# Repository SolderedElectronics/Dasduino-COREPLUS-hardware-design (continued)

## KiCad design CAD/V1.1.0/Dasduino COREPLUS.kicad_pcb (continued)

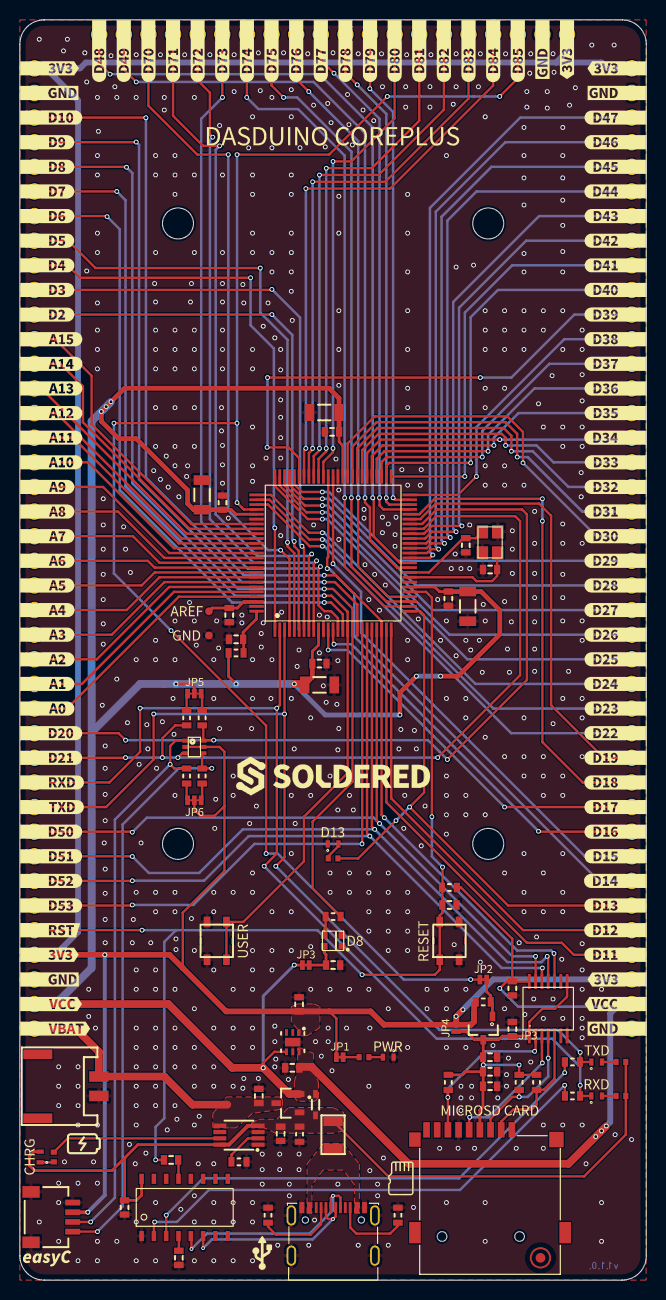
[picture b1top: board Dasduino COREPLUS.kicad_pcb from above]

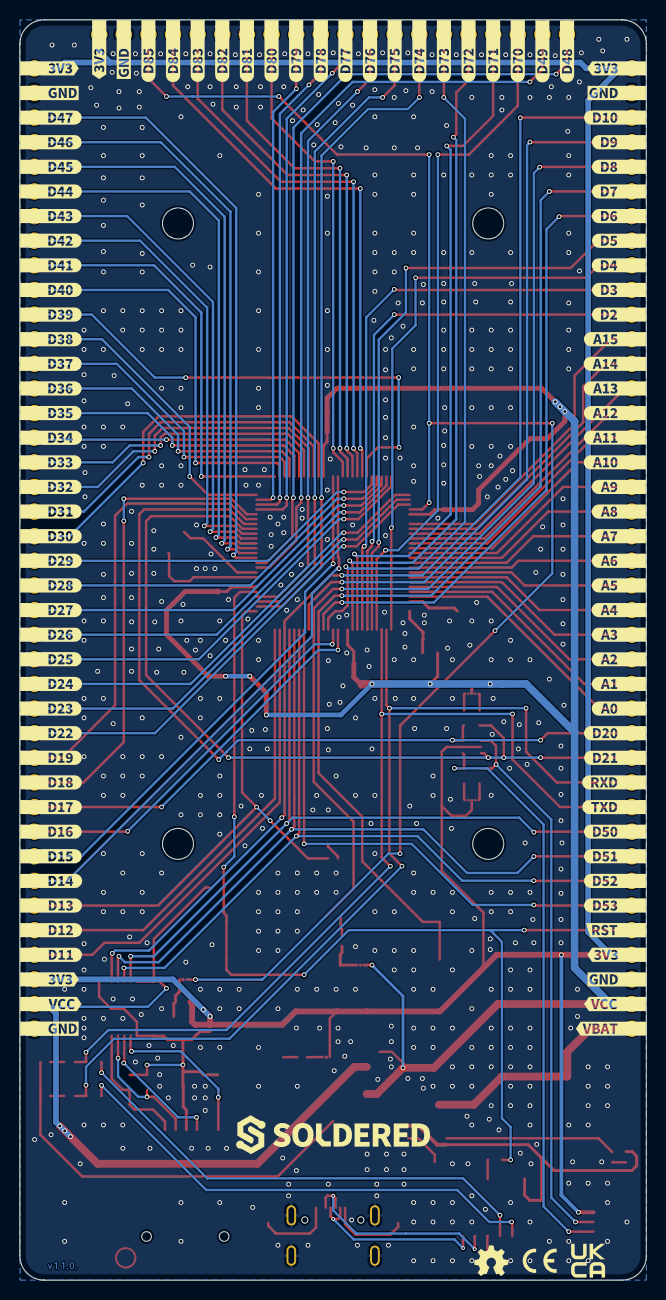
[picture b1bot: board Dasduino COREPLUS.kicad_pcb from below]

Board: 2 copper layers, 64.6 x 130.0 mm, 307 parts (104 on the bottom side), 127 nets.

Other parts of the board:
Ref**: Val**; Version1.1.0
kibuzzard-63D0D5A9: G***; kibuzzard-63D0D5A9
kibuzzard-63D0D5D8: G***; kibuzzard-63D0D5D8
kibuzzard-63D0D6BF: G***; kibuzzard-63D0D6BF
kibuzzard-63D0D6CA: G***; kibuzzard-63D0D6CA
kibuzzard-63D0D7E7: G***; kibuzzard-63D0D7E7
kibuzzard-63D0D78E: G***; kibuzzard-63D0D78E
kibuzzard-63D0D81B: G***; kibuzzard-63D0D81B
kibuzzard-63D0D88E: G***; kibuzzard-63D0D88E
kibuzzard-63D0DB6C: G***; kibuzzard-63D0DB6C
kibuzzard-63D0DB7A: G***; kibuzzard-63D0DB7A
kibuzzard-63D0DB98: G***; kibuzzard-63D0DB98
kibuzzard-63D0DBA8: G***; kibuzzard-63D0DBA8
kibuzzard-63D0DBC0: G***; kibuzzard-63D0DBC0
kibuzzard-63D0DBF0, kibuzzard-63D0DBF0#2: G***; kibuzzard-63D0DBF0
kibuzzard-63DB5B79: G***; kibuzzard-63DB5B79
kibuzzard-63DB5C1A: G***; kibuzzard-63DB5C1A
kibuzzard-63DB5C2A, kibuzzard-63DB5C2A#2: G***; kibuzzard-63DB5C2A
kibuzzard-63DB5CBE: G***; kibuzzard-63DB5CBE
kibuzzard-63DB5CD0: G***; kibuzzard-63DB5CD0
kibuzzard-63DB9B0F: G***; kibuzzard-63DB9B0F
kibuzzard-63DB9B4A: G***; kibuzzard-63DB9B4A
kibuzzard-63DB9B6F: G***; kibuzzard-63DB9B6F
kibuzzard-63DB9B22: G***; kibuzzard-63DB9B22
kibuzzard-63DB9B39: G***; kibuzzard-63DB9B39
kibuzzard-63DB9B82: G***; kibuzzard-63DB9B82
kibuzzard-63DB9B95: G***; kibuzzard-63DB9B95
kibuzzard-63DB9BB2: G***; kibuzzard-63DB9BB2
kibuzzard-63DB9BBC: G***; kibuzzard-63DB9BBC
kibuzzard-63DB9BC7: G***; kibuzzard-63DB9BC7
kibuzzard-63DB9BD1: G***; kibuzzard-63DB9BD1
kibuzzard-63DB9BDF: G***; kibuzzard-63DB9BDF
kibuzzard-63DB9BEA: G***; kibuzzard-63DB9BEA
kibuzzard-63DB9BF5: G***; kibuzzard-63DB9BF5
kibuzzard-63DB9C3D: G***; kibuzzard-63DB9C3D
kibuzzard-63DB9C05: G***; kibuzzard-63DB9C05
kibuzzard-63DB9C5F: G***; kibuzzard-63DB9C5F
kibuzzard-63DB9C6A: G***; kibuzzard-63DB9C6A
kibuzzard-63DB9C8D: G***; kibuzzard-63DB9C8D
kibuzzard-63DB9C18: G***; kibuzzard-63DB9C18
kibuzzard-63DB9C25: G***; kibuzzard-63DB9C25
kibuzzard-63DB9C31: G***; kibuzzard-63DB9C31
kibuzzard-63DB9C47: G***; kibuzzard-63DB9C47
kibuzzard-63DB9C52: G***; kibuzzard-63DB9C52
kibuzzard-63DB9C76: G***; kibuzzard-63DB9C76
kibuzzard-63DB9C82: G***; kibuzzard-63DB9C82
kibuzzard-63DB9C97: G***; kibuzzard-63DB9C97
kibuzzard-63DB9CA2: G***; kibuzzard-63DB9CA2
kibuzzard-63DB9CAE: G***; kibuzzard-63DB9CAE
kibuzzard-63DB9D1E: G***; kibuzzard-63DB9D1E
kibuzzard-63DB9D4E: G***; kibuzzard-63DB9D4E
kibuzzard-63DB9D5B: G***; kibuzzard-63DB9D5B
kibuzzard-63DB9D9C: G***; kibuzzard-63DB9D9C
kibuzzard-63DB9D42: G***; kibuzzard-63DB9D42
kibuzzard-63DB9D68: G***; kibuzzard-63DB9D68
kibuzzard-63DB9D76: G***; kibuzzard-63DB9D76
kibuzzard-63DB9D81: G***; kibuzzard-63DB9D81
kibuzzard-63DB9D90: G***; kibuzzard-63DB9D90
kibuzzard-63DB9DA8: G***; kibuzzard-63DB9DA8
kibuzzard-63DB9DB6: G***; kibuzzard-63DB9DB6
kibuzzard-63DB9DC9: G***; kibuzzard-63DB9DC9
kibuzzard-63DB9DD3: G***; kibuzzard-63DB9DD3
kibuzzard-63DB9DE3: G***; kibuzzard-63DB9DE3
kibuzzard-63DB9DF0: G***; kibuzzard-63DB9DF0
kibuzzard-63DB9E4D: G***; kibuzzard-63DB9E4D
kibuzzard-63DB9E5A: G***; kibuzzard-63DB9E5A
kibuzzard-63DB9E8E: G***; kibuzzard-63DB9E8E
kibuzzard-63DB9E9A: G***; kibuzzard-63DB9E9A
kibuzzard-63DB9E16: G***; kibuzzard-63DB9E16
kibuzzard-63DB9E22: G***; kibuzzard-63DB9E22
kibuzzard-63DB9E42: G***; kibuzzard-63DB9E42
kibuzzard-63DB9E68: G***; kibuzzard-63DB9E68
kibuzzard-63DB9E75: G***; kibuzzard-63DB9E75
kibuzzard-63DB9E80: G***; kibuzzard-63DB9E80
kibuzzard-63DB9EA7: G***; kibuzzard-63DB9EA7
kibuzzard-63DB9EB7: G***; kibuzzard-63DB9EB7
kibuzzard-63DB9EC3: G***; kibuzzard-63DB9EC3
kibuzzard-63DB9ED0: G***; kibuzzard-63DB9ED0
kibuzzard-63DB9EDD: G***; kibuzzard-63DB9EDD
kibuzzard-63DB9EE9: G***; kibuzzard-63DB9EE9
kibuzzard-63DB9F7D: G***; kibuzzard-63DB9F7D
kibuzzard-63DB9F8B: G***; kibuzzard-63DB9F8B
kibuzzard-63DB9F37: G***; kibuzzard-63DB9F37
kibuzzard-63DB9F59: G***; kibuzzard-63DB9F59
kibuzzard-63DB9F65: G***; kibuzzard-63DB9F65
kibuzzard-63DB9F70: G***; kibuzzard-63DB9F70
kibuzzard-63DB9FAF: G***; kibuzzard-63DB9FAF
kibuzzard-63DB9FB8: G***; kibuzzard-63DB9FB8
kibuzzard-63DB9FC0: G***; kibuzzard-63DB9FC0
kibuzzard-63DB9FC8: G***; kibuzzard-63DB9FC8
kibuzzard-63DB9FD5: G***; kibuzzard-63DB9FD5
kibuzzard-63DB9FE4: G***; kibuzzard-63DB9FE4
kibuzzard-63DB9FEE: G***; kibuzzard-63DB9FEE
kibuzzard-63DB5956: G***; kibuzzard-63DB5956
kibuzzard-63DBA0A5: G***; kibuzzard-63DBA0A5
kibuzzard-63DBA0B0: G***; kibuzzard-63DBA0B0
kibuzzard-63DBA0B9: G***; kibuzzard-63DBA0B9
kibuzzard-63DBA1AD: G***; kibuzzard-63DBA1AD
kibuzzard-63DBA1B8: G***; kibuzzard-63DBA1B8
kibuzzard-63DBA1C2: G***; kibuzzard-63DBA1C2
kibuzzard-63DBA1CC: G***; kibuzzard-63DBA1CC
kibuzzard-63DBA1D6: G***; kibuzzard-63DBA1D6
kibuzzard-63DBA1E0: G***; kibuzzard-63DBA1E0
kibuzzard-63DBA1EC: G***; kibuzzard-63DBA1EC
kibuzzard-63DBA1FB: G***; kibuzzard-63DBA1FB
kibuzzard-63DBA2A7: G***; kibuzzard-63DBA2A7
kibuzzard-63DBA2AF: G***; kibuzzard-63DBA2AF
kibuzzard-63DBA2B9: G***; kibuzzard-63DBA2B9
kibuzzard-63DBA2C2: G***; kibuzzard-63DBA2C2
kibuzzard-63DBA2CC: G***; kibuzzard-63DBA2CC
kibuzzard-63DBA02D: G***; kibuzzard-63DBA02D
kibuzzard-63DBA2D7: G***; kibuzzard-63DBA2D7
kibuzzard-63DBA2FF: G***; kibuzzard-63DBA2FF
kibuzzard-63DBA04D: G***; kibuzzard-63DBA04D
kibuzzard-63DBA5C2: G***; kibuzzard-63DBA5C2
kibuzzard-63DBA06B: G***; kibuzzard-63DBA06B
kibuzzard-63DBA07D: G***; kibuzzard-63DBA07D
kibuzzard-63DBA08C: G***; kibuzzard-63DBA08C
kibuzzard-63DBA09E: G***; kibuzzard-63DBA09E
kibuzzard-63DBA011: G***; kibuzzard-63DBA011
kibuzzard-63DBA14D: G***; kibuzzard-63DBA14D
kibuzzard-63DBA17F: G***; kibuzzard-63DBA17F
kibuzzard-63DBA18A: G***; kibuzzard-63DBA18A
kibuzzard-63DBA019: G***; kibuzzard-63DBA019
kibuzzard-63DBA024: G***; kibuzzard-63DBA024
kibuzzard-63DBA25A: G***; kibuzzard-63DBA25A
kibuzzard-63DBA28C: G***; kibuzzard-63DBA28C
kibuzzard-63DBA29D: G***; kibuzzard-63DBA29D
kibuzzard-63DBA31E: G***; kibuzzard-63DBA31E
kibuzzard-63DBA33C: G***; kibuzzard-63DBA33C
kibuzzard-63DBA35B: G***; kibuzzard-63DBA35B
kibuzzard-63DBA038: G***; kibuzzard-63DBA038
kibuzzard-63DBA043: G***; kibuzzard-63DBA043
kibuzzard-63DBA056: G***; kibuzzard-63DBA056
kibuzzard-63DBA060: G***; kibuzzard-63DBA060
kibuzzard-63DBA60B: G***; kibuzzard-63DBA60B
kibuzzard-63DBA075: G***; kibuzzard-63DBA075
kibuzzard-63DBA085: G***; kibuzzard-63DBA085
kibuzzard-63DBA093: G***; kibuzzard-63DBA093
kibuzzard-63DBA106: G***; kibuzzard-63DBA106
kibuzzard-63DBA110: G***; kibuzzard-63DBA110
kibuzzard-63DBA157: G***; kibuzzard-63DBA157
kibuzzard-63DBA240: G***; kibuzzard-63DBA240
kibuzzard-63DBA264: G***; kibuzzard-63DBA264
kibuzzard-63DBA270: G***; kibuzzard-63DBA270
kibuzzard-63DBA279: G***; kibuzzard-63DBA279
kibuzzard-63DBA282: G***; kibuzzard-63DBA282
kibuzzard-63DBA295: G***; kibuzzard-63DBA295
kibuzzard-63DBA308: G***; kibuzzard-63DBA308
kibuzzard-63DBA315: G***; kibuzzard-63DBA315
kibuzzard-63DBA329: G***; kibuzzard-63DBA329
kibuzzard-63DBA332: G***; kibuzzard-63DBA332
kibuzzard-63DBA346: G***; kibuzzard-63DBA346
kibuzzard-63DBA352: G***; kibuzzard-63DBA352
kibuzzard-63DBA366: G***; kibuzzard-63DBA366
kibuzzard-63DBA594: G***; kibuzzard-63DBA594
kibuzzard-63DBA652: G***; kibuzzard-63DBA652
kibuzzard-63DBA679: G***; kibuzzard-63DBA679
kibuzzard-64B794A8, kibuzzard-64B794A8#2: G***; kibuzzard-64B794A8
kibuzzard-64B794B0, kibuzzard-64B794B0#2: G***; kibuzzard-64B794B0
kibuzzard-64B794BC, kibuzzard-64B794BC#2: G***; kibuzzard-64B794BC
kibuzzard-64B794C8, kibuzzard-64B794C8#2: G***; kibuzzard-64B794C8
kibuzzard-64B794D8, kibuzzard-64B794D8#2: G***; kibuzzard-64B794D8
kibuzzard-64B794E2, kibuzzard-64B794E2#2: G***; kibuzzard-64B794E2
kibuzzard-64B794F0, kibuzzard-64B794F0#2: G***; kibuzzard-64B794F0
kibuzzard-64B794FA, kibuzzard-64B794FA#2: G***; kibuzzard-64B794FA
kibuzzard-64B7949A, kibuzzard-64B7949A#2: G***; kibuzzard-64B7949A
kibuzzard-64B7950D, kibuzzard-64B7950D#2: G***; kibuzzard-64B7950D
kibuzzard-64B7951A, kibuzzard-64B7951A#2: G***; kibuzzard-64B7951A
kibuzzard-64B7952A, kibuzzard-64B7952A#2: G***; kibuzzard-64B7952A
kibuzzard-64B7953B, kibuzzard-64B7953B#2: G***; kibuzzard-64B7953B
kibuzzard-64B79148: G***; kibuzzard-64B79148
kibuzzard-64B79150: G***; kibuzzard-64B79150
kibuzzard-64B79501, kibuzzard-64B79501#2: G***; kibuzzard-64B79501
kibuzzard-64B79524, kibuzzard-64B79524#2: G***; kibuzzard-64B79524
kibuzzard-64B79532, kibuzzard-64B79532#2: G***; kibuzzard-64B79532
kibuzzard-64D5E88C: G***; kibuzzard-64D5E88C
kibuzzard-64736A4E, kibuzzard-64736A4E#2: G***; kibuzzard-64736A4E
kibuzzard-64736A30, kibuzzard-64736A30#2: G***; kibuzzard-64736A30
kibuzzard-64736B29, kibuzzard-64736B29#2: G***; kibuzzard-64736B29
kibuzzard-64736B32, kibuzzard-64736B32#2: G***; kibuzzard-64736B32
kibuzzard-64736DE1: G***; kibuzzard-64736DE1
kibuzzard-647344B7: G***; kibuzzard-647344B7
kibuzzard-6473446E: G***; kibuzzard-6473446E
kibuzzard-6473447C: G***; kibuzzard-6473447C
kibuzzard-6473450E: G***; kibuzzard-6473450E
kibuzzard-6473451D: G***; kibuzzard-6473451D
kibuzzard-6473453E: G***; kibuzzard-6473453E
kibuzzard-6473454B: G***; kibuzzard-6473454B
kibuzzard-6473467D: G***; kibuzzard-6473467D
kibuzzard-6473468F: G***; kibuzzard-6473468F
kibuzzard-64734485: G***; kibuzzard-64734485
kibuzzard-64734490: G***; kibuzzard-64734490
kibuzzard-64734502: G***; kibuzzard-64734502
kibuzzard-64734552: G***; kibuzzard-64734552
kibuzzard-64734662: G***; kibuzzard-64734662
kibuzzard-64734674: G***; kibuzzard-64734674
kibuzzard-64734686: G***; kibuzzard-64734686

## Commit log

2024-10-20 Updating open source files.
